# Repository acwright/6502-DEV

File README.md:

6502-DEV
========

An **AC6502** retro-style 8-bit computer based on the **65C02** microprocessor.

> 📖 **Guide:** [AC6502 Documentation](https://acwright.github.io/6502-DOCS/) — the user's and programmer's guide for the whole family.
> See [DEV's page in the family appendix](https://acwright.github.io/6502-DOCS/family/dev).

---

**Building one? Every part you need, with supplier numbers and known issues, is in [BOM.md](BOM.md).**

## Table of Contents

- [Overview](#overview)
- [Architecture](#architecture)
- [Systems](#systems)
- [Software](#software)
- [Hardware](#hardware)
  - [DEV Board](#dev-board)
  - [DEV Output Board](#dev-output-board)
  - [DEV LCD Board](#dev-lcd-board)
- [Which revision to make](#which-revision-to-make)
- [Works with the stock BIOS](#works-with-the-stock-bios)
- [Firmware](#firmware)
  - [DB Emulator](#db-emulator)
  - [DOB Display](#dob-display)
- [CAD](#cad)
- [Production](#production)
- [Schematics](#schematics)
- [Shared lines](#shared-lines)
- [Extra pins: `EXP0`–`EXP3` and `HRDB`](#extra-pins-exp0exp3-and-hrdb)
- [Jumpers](#jumpers)
- [Off-board headers](#off-board-headers)
- [Libraries](#libraries)
- [Bill of Materials](#bill-of-materials)
- [License](#license)

---

## Overview

The AC6502 ecosystem is a family of open-source, 65C02-based computers sharing a common architecture, memory map, and [BIOS](https://github.com/acwright/6502-BIOS). Each computer in the family is purpose-built for a different use case but runs the same software and firmware.

The **DEV** is an emulation-based development system. It replaces the physical 65C02 CPU with a [Teensy 4.1](https://www.pjrc.com/store/teensy41.html) running cycle-accurate 65C02 emulation via [vrEmu6502](https://github.com/visrealm/vrEmu6502).
## Architecture

All AC6502 computers share:

- **CPU**: 65C02 (or accurate emulation)
- **Memory**: 32KB RAM + 32KB ROM, with optional banked RAM expansion
- **Memory Map**: Standardized across the ecosystem — zero page, stack, I/O space ($8000–$9FFF), system ROM, and interrupt vectors at $FFFA–$FFFF
- **Bus**: 16-bit address bus, 8-bit bidirectional data bus, standard 65C02 control signals (RW, PHI2, RESET, IRQ, NMI, RDY, SYNC)
- **BIOS**: A common [BIOS](https://github.com/acwright/6502-BIOS) provides the kernel, monitor, and BASIC interpreter across all systems

## Systems

| Project | Description |
|---------|-------------|
| [6502-ACE](https://github.com/acwright/6502-ACE) | All-in-one Computer Experience — A single board computer |
| [6502-COB](https://github.com/acwright/6502-COB) | Computer On a Backplane — Modular desktop computer with expandable card slots |
| [6502-DEV](https://github.com/acwright/6502-DEV) | Development Environment Vehicle — Emulation-based dev system (YOU ARE HERE) |
| [6502-KIM](https://github.com/acwright/6502-KIM) | Keypad Input Monitor - KIM-1 inspired minimal computer |
| [6502-VCS](https://github.com/acwright/6502-VCS) | Video Computer System — Cartridge-based retro gaming console |

## Software

| Project | Description |
|---------|-------------|
| [6502-BIOS](https://github.com/acwright/6502-BIOS) | The shared BIOS (kernel, monitor, BASIC) for all AC6502 computers |
| [6502-EMULATOR](https://github.com/acwright/6502-EMULATOR) | Emulator for the whole family — desktop app, browser build, and a command line for scripted runs |
| [6502-PRG](https://github.com/acwright/6502-PRG) | Template project for writing assembly language programs |
| [6502-CRT](https://github.com/acwright/6502-CRT) | Template project for writing assembly language cartridges |
| [6502-ASM](https://github.com/acwright/6502-ASM) | Assembly language example programs and demos |
| [6502-BAS](https://github.com/acwright/6502-BAS) | BASIC program listings |
| [6502-WOZMON](https://github.com/acwright/6502-WOZMON) | Wozmon as a standalone ROM |
| [6502-NOP](https://github.com/acwright/6502-NOP) | An all-NOP ROM, for probing a board during bring-up |
| [6502-DOCS](https://github.com/acwright/6502-DOCS) | The documentation site — the guide, the printable reference cards, branding and label artwork |
| [cffs](https://github.com/acwright/cffs) | Builds CompactFlash disk images for the BIOS filesystem |
| [bastok](https://github.com/acwright/bastok) | Tokenizes BASIC listings into `.prg` images, and back |
| [bin2woz](https://github.com/acwright/bin2woz) | Converts a binary into a Wozmon serial upload |

## Hardware

This repository contains KiCad 7.0+ PCB designs for the boards of the DEV system: the two that make it up, and an LCD board for its bus.

### DEV Board
`Hardware/DEV Board/`

The main board hosting the Teensy 4.1. Provides 65C02 bus emulation, SD card storage, Ethernet, USB keyboard/joystick input, and hardware control buttons (Run/Stop, Step, Reset, Frequency). Includes a bus connector and card slot with level shifters for optional real hardware expansion.

### DEV Output Board
`Hardware/DEV Output Board/`

The AV output board hosting a Teensy 4.0 and a 2.4" ILI9341 TFT LCD. Emulates a TMS9918A Video Display Processor and a MOS 6581 SID audio synthesizer, driven in real time via high-speed serial from the DEV Board. The DEV Board sends the same AV packets over USB at the same time, so a browser can render the output in parallel with this board — the two paths are simultaneous, not alternatives.

### DEV LCD Board
`Hardware/DEV LCD Board/`

A 320×240 TFT LCD (an Adafruit 2.8" ILI9341 breakout) driven through a 65C22 VIA, on the AC6502 bus. Rev 1.0 was made as the COB LCD Board, and its silkscreen says `6502 LCD BOARD`; it moved here on 2026-11-14.

<!-- Which revision to make: generated by Tools/revision-audit/register.py from Tools/data/orders.json. Edit that file, not this section. -->
## Which revision to make

**Make the newest revision of a board, and check its label first.** The table below gives each board's newest revision. A newer revision fixes what was found on the older ones. Every revision, old and new, is in [REVISIONS.md](REVISIONS.md), with what changed in each.

Each revision carries one of three labels:

- **Tested:** This revision was built and tested.
- **Proven design:** Not built at this revision, but its circuit is proven. Either it is a tested revision's circuit, or each change copies a circuit built and tested on another board or on the bench, or is a textbook circuit that leaves everything the tested revision does as it was. Any other change is silkscreen text, part values, mounting holes, outline clean-up, parts moved a fraction of a millimetre onto their grid, capacitor pitch, socket outlines, a footprint swap with the same holes, a solder jumper's default, the solder mask or paste at a card edge, or tracks rerouted or pours refilled with DRC and the netlist check passing. A builder can treat it as tested.
- **Untested:** The circuit, the power path or the layout changed in a way that only a built board proves, or the board has never been built at all.

[BOM.md](BOM.md) has the parts for every revision, and its known issues.

| Board | Newest revision | Label | Why |
|---|---|---|---|
| DEV Board | 1.1 | **Proven design** | Rev 1.0's circuit, except that J6's CC resistors pull up to `5V_HOST` (56 kΩ), as a USB-C host's should, where Rev 1.0 pulls them down. Nothing Rev 1.0 was tested with changes. Two designators moved. |
| DEV LCD Board | 1.1 | **Proven design** | The DEV's name in the logo, JLCPCB's marker removed; silkscreen only. |
| DEV Output Board | 1.1 | **Proven design** | Silkscreen text only. |
<!-- End of which revision to make -->

<!-- Stock BIOS: generated by Tools/bios/gen.py from Tools/data/bios.json. Edit that file, not this section. -->
## Works with the stock BIOS

Whether each board works with the stock BIOS, and what it takes if not. The stock BIOS for the DEV is **BIOS 1.x**, from the `v1.x` branch of [6502-BIOS](https://github.com/acwright/6502-BIOS). The ACE runs BIOS 2.x, for a 6502-PICOVDP. The DEV can't run BIOS 2.x yet: its DB Emulator firmware is written for BIOS 1.x. The BIOS looks for each card in its own 1 KB window at boot, and uses only what it finds.

- **Compatible:** the BIOS finds the board and uses it, built from its parts list with the jumpers the [Jumpers](#jumpers) table gives. A card counts only on the window the BIOS expects; on another window it's the builder's experiment.
- **After a step:** it works once the builder does what the entry names, beyond the parts list and the jumpers.
- **Not used by the BIOS:** safe beside it, but your own software drives it.
- **Nothing to support:** the board has no registers for the BIOS to find, such as a backplane, a helper behind a card, or a cartridge's programmer.

| Board | Rev | Stock BIOS | Why | Source |
|---|---|---|---|---|
| DEV Board | 1.0, 1.1 | **Compatible** | Its Teensy 4.1 runs `BIOS.bin` from its SD card on an emulated 65C02, with every card the BIOS looks for emulated in its window, IO 1 to IO 8. | [DB Emulator](Firmware/DB%20Emulator/README.md) |
| DEV LCD Board | 1.0, 1.1 | **Not used by the BIOS** | The BIOS doesn't look for it: its 65C22 VIA goes in a window no other card uses, and your own software drives the LCD. | README [Jumpers](#jumpers) |
| DEV Output Board | 1.0, 1.1 | **Nothing to support** | No registers on the bus: it shows the DEV Board's emulated video and plays its emulated SID, sent over serial. | [DB Emulator](Firmware/DB%20Emulator/README.md) |

<!-- End of stock BIOS -->

## Firmware

This repository contains [PlatformIO](https://platformio.org/)-based firmware for both boards.

### DB Emulator
`Firmware/DB Emulator/`

Firmware for the Teensy 4.1 on the DEV Board. Provides:

- Cycle-accurate 65C02 emulation
- SD card ROM/cartridge/program loading and memory snapshots
- Ethernet with mDNS (`6502.local`) and an embedded web control interface
- USB keyboard and joystick support (Xbox 360/One)
- AV packet output to both destinations at once — over USB to the browser (Web Serial API) and over hardware UART at 6 Mbps to the DOB Display
- Serial terminal interface (115200 baud)
- Hardware button control (Run/Stop, Step, Reset, Frequency)
- Variable CPU clock speed

See [Firmware/DB Emulator/README.md](./Firmware/DB%20Emulator/README.md) for setup and usage instructions.

### DOB Display
`Firmware/DOB Display/`

Firmware for the Teensy 4.0 on the DEV Output Board. Provides:

- TMS9918A VDP emulation (all four display modes, 256×192 active area)
- MOS 6581 SID audio emulation (3 voices, ADSR envelopes, PWM audio output)
- AV packet stream input at 6 Mbps over hardware UART from the DB Emulator (which also streams the same packets over USB to the browser)

See [Firmware/DOB Display/README.md](./Firmware/DOB%20Display/README.md) for setup and usage instructions.

## CAD
`CAD/`

3D-printable enclosure parts and laser-cut top panels for the DEV system.

**Board images** are in `CAD/Images/<Board>/Rev X/`: `Front.png` and `Back.png` on white, and `Front Transparent.png` and `Back Transparent.png` with no background. Every image is a 3D render at the same size, with the black solder mask and white silkscreen the boards are made with. Bare-board photos may differ, because the renders show parts fitted.

**Top panels are versioned by board revision**, like `Hardware/`: `CAD/Tops/<Board>/Rev X/`. Each revision has its own complete folder, even when two revisions share the same files. `Bases/` holds the parts for a whole computer, not for one board, so it isn't versioned.

The **[plate mounting drawing](CAD/Bases/Plate%20Mounting%20Drawing.png)** ([SVG](CAD/Bases/Plate%20Mounting%20Drawing.svg)) shows where the DEV Board and the DEV Output Board mount on the base plate, with every hole's position and the hardware the build needs. The plate is a stack of three 3 mm acrylic layers.

## Production
`Production/`

[REVISIONS.md](REVISIONS.md) lists every board revision: whether it was made, its JLCPCB order, the commit it was made from, and what fits it.

JLCPCB-ready Gerber files and BOM/CPL for PCB fabrication and assembly.

## Schematics
`Schematics/`

PDF schematics for each board.

## Shared lines

Five lines of the 6502 bus are shared by every board on it: `RESB`, `IRQB`, `NMIB`, `RDY` and `BE`. A board may pull one of these lines low, and nothing drives one high. Each line is held high by one 10kΩ pull-up resistor to VCC, on the board with the CPU: the ACE Board, the KIM Board, the VCS Main Board, the COB CPU Card or CPU Card Pro, or the DEV Board. No other board has one. Two pull-ups on the same line would sit in parallel and lower its resistance, so a card that adds its own pull-up changes the machine for every other board. The VIAs and PIAs in the BOMs, the W65C22N and W65C21N, have open-drain interrupt outputs for this reason.

**Interrupt outputs.** Whatever drives `IRQB` or `NMIB` may only pull it low. Every board is drawn for the parts in its BOM and works as shipped, with no jumper to cut or bridge:

- **A part whose interrupt output is open-drain** (the W65C22N, W65C21N, R6551AP, DS1511Y, DS1501 and TMS9918A) drives the line directly, or through a diode with a solder jumper across it that ships bridged. The diode is fitted either way. To use a part that drives its interrupt high as well as low instead, such as a W65C22S or a replacement of your own, cut the jumper: the diode then lets the part only pull the line low. A board with no diode in the line can't take such a part.
- **A part that drives its interrupt high as well as low** (the pico9918, the VERA module, and a microcontroller such as the ATmega1284 or a Raspberry Pi Pico) reaches the line through a diode, a BAT85 or a 1N914, with its cathode toward the part. Where a solder jumper sits across that diode, it ships open. The diode is then the only path to the line, so fit it, and never bridge the jumper, because the part would then hold the line high against every other interrupt source.
- **A microcontroller wired to the line directly,** as on the ACE Board, the Mega Helper and the Flash Helper, drives it open-drain in its firmware: it sets the pin low or leaves it as an input, and never drives it high.

The *Jumpers* section below gives each board's interrupt jumper.

The same holds where a board has its own reset circuit. A reset switch, its timer and the transistor that pulls `RESB` low can be on any board, such as the COB Backplane Pro or the Clock Card, but the `RESB` pull-up is only ever on the board with the CPU. Each of those boards draws its pull-ups together, in one group on its schematic.

The DEV Board is the exception on `RESB`. It stands in for a Main Board, so it owns reset: its Reset button goes to the Teensy, and the Teensy drives `RESB` onto the bus through U3, a level shifter that only sends signals out, as it drives `PHI2`. U3 holds `RESB` high or low, so the DEV Board has no `RESB` pull-up, and nothing else on its bus may pull `RESB` low. Connect a DEV only to a passive backplane, never to the COB Backplane Pro, whose reset circuit would pull against U3, and don't fit a card that pulls `RESB` low, such as the COB RTC Card.

`SOB` is a CPU pin that isn't on the bus. It is tied to VCC, directly or through a 10kΩ resistor.

A few chips have a pull-up of their own inside the chip, such as an ATmega's reset pin. Where such a pin is wired to `RESB`, its pull-up of 30–60kΩ sits in parallel with the 10kΩ one. That's harmless, because whatever pulls `RESB` low can sink the extra current many times over.

A revision that doesn't follow this yet says so in its known issues in [BOM.md](BOM.md), with what to fit or remove.

## Extra pins: `EXP0`–`EXP3` and `HRDB`

`EXP` stands for "extra pin". Four pins of the 6502 bus are left for a builder's own use: pin 4 is `EXP1`, pin 6 is `EXP0`, pin 19 is `EXP3` and pin 21 is `EXP2`.

Pins 4 and 6 have a second job. A cartridge ties both of them to GND. That pulls `HRDB` ("High ROM disable bar", active low) low on the board with the ROM, which takes `$C000–$FFFF` away from the ROM so that the cartridge answers there instead. So in a build that uses cartridges, pins 4 and 6 are reserved for `HRDB`, and nothing else may drive them. They are free as `EXP1` and `EXP0` only in a build that never uses cartridges. `EXP2` and `EXP3` are always free.

How the boards treat pins 4 and 6:

- **The ACE Board and the KIM Board** join them to their ROM's `HRDB` input, and their silk says `HRDB`. The VCS Main Board joins them the same way from Rev 1.1.
- **The COB Memory Card** joins them to its `HRDB` only through jumpers: fit two shunts on J2, or bridge JP1 and JP2, in a COB that takes cartridges. It is the only board with these jumpers, because the COB is the experimenter's build. The VCS Main Board Rev 1.0 had them too (J5, or JP3 and JP4); fit them, because the VCS always takes cartridges.
- **A cartridge** (the ROM Cart, the Flash Cart, the KIM Keypad Card) ties them to GND.
- **A board that only carries the bus through**, such as a backplane or a helper, calls them `EXP1` and `EXP0`, as its silk does, and a note on its schematic says what they carry.

<!-- Jumpers: generated by Tools/jumpers/gen.py from Tools/data/jumpers.json. Edit that file, not this section. -->
## Jumpers

Some boards have solder jumpers, and pin headers that take a shunt. The tables below give every one: what it's for, how the board is shipped, and what to do with it. The **Needed** column marks the ones that matter:

- **To run**: the board doesn't work until this is set. Set it before the first power-up.
- **For serial**, **For interrupts**, **For cartridges**: the board runs without it, but that feature doesn't.
- Blank: leave it as shipped unless you want what it offers.

Where a header needs a shunt, the board's BOM lists it.

**DEV LCD Board**

| Rev | Jumper | What it's for | As shipped | What to do | Needed |
|---|---|---|---|---|---|
| 1.0, 1.1 | J2 | I/O window: one shunt picks the 1 KB window the board answers in. | No shunt. | Fit the shunt beside a window no other card uses. The BIOS doesn't look for this board. | To run |
| 1.0, 1.1 | JP1 | Across D2, the diode in the W65C22N's interrupt line. | Bridged. | Leave it. The W65C22N's interrupt output is open-drain: it only pulls the line low, so the board works as shipped and D2 isn't needed. To fit a part that drives its interrupt high as well as low, such as a W65C22S, cut JP1 so the interrupt goes through D2. |  |

<!-- End of jumpers -->

<!-- Off-board headers: generated by Tools/offboard/gen.py from Tools/offboard/offboard.json, Tools/data/offboard.json and the PCB files. Edit those, not this section. -->
## Off-board headers

Some boards have small headers, such as `RESET SW`, `CLOCK ENBL SW`, `POWER LED` and `VCC`, that a standard build leaves empty. They are for a machine built into a full enclosure, which AC6502 doesn't offer today. In such a build, the parts a person handles are mounted on the case and wired to the board through these headers: the power jack, the switches, the LEDs and the keyboard. The matching parts on the board are then left off. For example, an ACE Board can sit inside a case with its power jack, power switch and key switches left off, and a Keyboard Helper as its keyboard.

To build a board for a case:

1. Fit the header, and wire the part on the case to it. The table says what goes on each pin.
2. Leave off the parts on the board that the table names. A button on the case can work beside the board's own button, but some parts, such as an LED that shares the board's resistor, can't share.
3. Set any jumper the table mentions. The [Jumpers](#jumpers) section has the rest.

The connector follows the kind of build. A single-board machine, the ACE Board or the KIM Board, uses plain 2.54 mm pin headers, which are simpler and cheaper. A board in a multi-board machine, every COB board and the separate boards of the VCS, the DEV and the KIM, uses JST XH, the family's standard for these headers.

The table lists every off-board header on each board's newest revision, read from the board's PCB file.

| Board | Rev | Header | Label | Connector | What it's for | Leave off |
|---|---|---|---|---|---|---|
| DEV Board | 1.1 | J3 | `PANEL` | Pin header, 2×4, 2.54 mm | Four buttons on the case, each between its pin and ground: Run/Stop on pin 1, Step on pin 3, Clock on pin 5 and Reset on pin 7. Pins 2, 4, 6 and 8 are ground. Each button is wired across one of SW1–SW4, the board's own buttons. | SW1–SW4, if the case covers them. Both sets of buttons work if they stay. |

<!-- End of off-board headers -->

## Libraries
`Libraries/`

Shared KiCad symbol and footprint libraries used across all AC6502 hardware projects, with their 3D models in `Models/`. A part is named for what it is and its shape, such as `RJ45 Jack LED` or `CR2032 Holder`, never for a manufacturer's part number, so a replacement part with the same footprint fits without renaming anything. The part numbers to buy are in [BOM.md](BOM.md). Every AC6502 repository carries the same copy of each part.

## Bill of Materials

Every part for every board, by revision, is in **[BOM.md](BOM.md)**, with supplier numbers, known issues, build notes and files to upload to Digi-Key and Mouser. What changed in each revision, and what is known about each one, is in **[REVISIONS.md](REVISIONS.md)**.

## License

Hardware designs are released under the [CERN Open Hardware Licence Version 2 – Permissive](https://ohwr.org/cern_ohl_p_v2.txt).  
Firmware is released under the MIT License — [DB Emulator](./Firmware/DB%20Emulator/LICENSE), [DOB Display](./Firmware/DOB%20Display/LICENSE).

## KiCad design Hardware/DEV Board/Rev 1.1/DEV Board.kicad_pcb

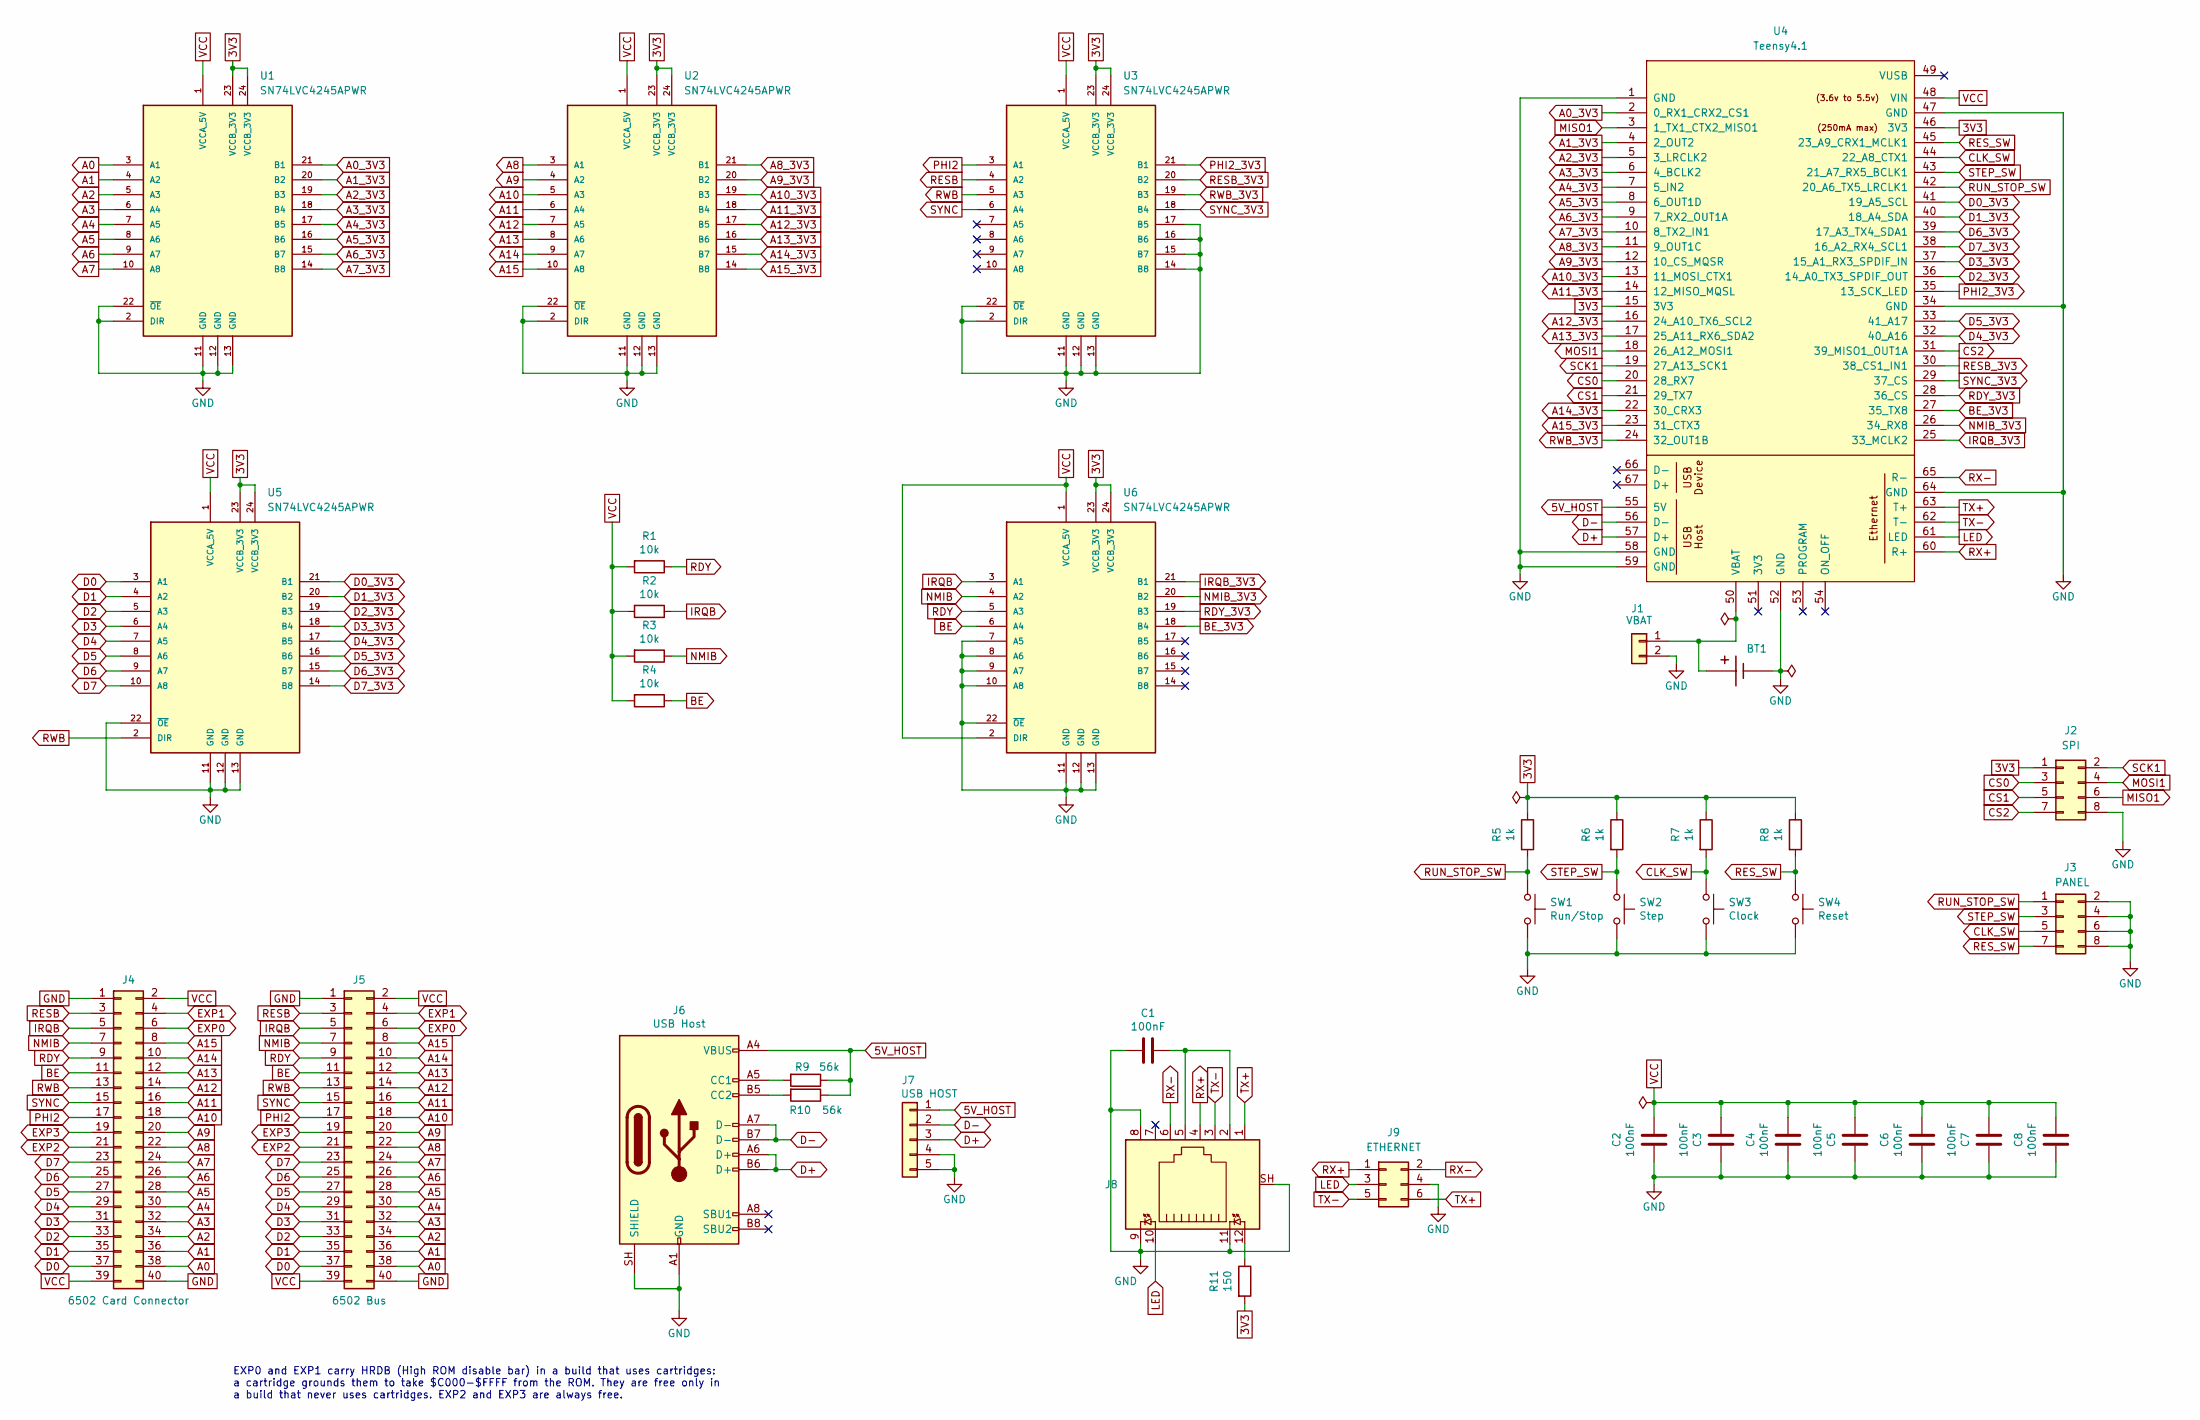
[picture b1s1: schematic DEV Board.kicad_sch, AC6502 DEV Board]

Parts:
BT1: CR2032; CR2032 Holder; Digikey 343-BAT-HLD-001-THM-TRCT-ND
C1, C2, C3, C4, C5, C6, C7, C8: 100nF; C_0805_2012Metric; LCSC C49678
J1: VBAT; PinHeader_1x02_P2.54mm_Vertical; Digikey S1011EC-40-ND
J2: SPI; PinHeader_2x04_P2.54mm_Vertical; Digikey S2011EC-40-ND
J3: PANEL; PinHeader_2x04_P2.54mm_Vertical; Digikey S2011EC-40-ND
J4: 6502 Card Connector; 6502 Card Slot; Digikey A31723-ND
J5: 6502 Bus; 6502 Bus Connector; Digikey 732-5401-ND
J6: USB Host; USB_C_Receptacle_HRO_TYPE-C-31-M-12; LCSC C2988369
J7: USB HOST; PinHeader_1x05_P2.54mm_Vertical; Digikey S1011EC-40-ND
J8: RJ45_LED; RJ45 Jack LED; Digikey 931-TMJDD111B083FC2A1D-ND
J9: ETHERNET; PinHeader_2x03_P2.00mm_Vertical; Digikey 2057-2PH2-06-UA-ND
R1, R2, R3, R4: 10k; R_0805_2012Metric; LCSC C17414
R5, R6, R7, R8: 1k; R_0805_2012Metric; LCSC C17513
R9, R10: 56k; R_0805_2012Metric; LCSC C169923
R11: 150; R_0805_2012Metric; LCSC C17471
SW1: Run/Stop; Tact Switch SMD 5.1mm; LCSC C318884
SW2: Step; Tact Switch SMD 5.1mm; LCSC C318884
SW3: Clock; Tact Switch SMD 5.1mm; LCSC C318884
SW4: Reset; Tact Switch SMD 5.1mm; LCSC C318884
U1, U2, U3, U5, U6: SN74LVC4245APWR; TSSOP-24_4.4x7.8mm_P0.65mm; LCSC C7859
U4: Teensy4.1; Teensy41

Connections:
3V3: J2.1, R5.1, R6.1, R7.1, R8.1, R11.2, U1.23 (VCCB_3V3), U1.24 (VCCB_3V3), U2.23 (VCCB_3V3), U2.24 (VCCB_3V3), U3.23 (VCCB_3V3), U3.24 (VCCB_3V3), U4.15 (3V3), U4.46 (3V3), U5.23 (VCCB_3V3), U5.24 (VCCB_3V3), U6.23 (VCCB_3V3), U6.24 (VCCB_3V3)
5V_HOST: J6.A4 (VBUS), J6.A9 (VBUS), J6.B4 (VBUS), J6.B9 (VBUS), J7.1, R9.1, R10.1, U4.55 (5V)
A0: J4.38, J5.38, U1.3 (A1)
A0_3V3: U1.21 (B1), U4.2 (0_RX1_CRX2_CS1)
A1: J4.36, J5.36, U1.4 (A2)
A1_3V3: U1.20 (B2), U4.4 (2_OUT2)
A2: J4.34, J5.34, U1.5 (A3)
A2_3V3: U1.19 (B3), U4.5 (3_LRCLK2)
A3: J4.32, J5.32, U1.6 (A4)
A3_3V3: U1.18 (B4), U4.6 (4_BCLK2)
A4: J4.30, J5.30, U1.7 (A5)
A4_3V3: U1.17 (B5), U4.7 (5_IN2)
A5: J4.28, J5.28, U1.8 (A6)
A5_3V3: U1.16 (B6), U4.8 (6_OUT1D)
A6: J4.26, J5.26, U1.9 (A7)
A6_3V3: U1.15 (B7), U4.9 (7_RX2_OUT1A)
A7: J4.24, J5.24, U1.10 (A8)
A7_3V3: U1.14 (B8), U4.10 (8_TX2_IN1)
A8: J4.22, J5.22, U2.3 (A1)
A8_3V3: U2.21 (B1), U4.11 (9_OUT1C)
A9: J4.20, J5.20, U2.4 (A2)
A9_3V3: U2.20 (B2), U4.12 (10_CS_MQSR)
A10: J4.18, J5.18, U2.5 (A3)
A10_3V3: U2.19 (B3), U4.13 (11_MOSI_CTX1)
A11: J4.16, J5.16, U2.6 (A4)
A11_3V3: U2.18 (B4), U4.14 (12_MISO_MQSL)
A12: J4.14, J5.14, U2.7 (A5)
A12_3V3: U2.17 (B5), U4.16 (24_A10_TX6_SCL2)
A13: J4.12, J5.12, U2.8 (A6)
A13_3V3: U2.16 (B6), U4.17 (25_A11_RX6_SDA2)
A14: J4.10, J5.10, U2.9 (A7)
A14_3V3: U2.15 (B7), U4.22 (30_CRX3)
A15: J4.8, J5.8, U2.10 (A8)
A15_3V3: U2.14 (B8), U4.23 (31_CTX3)
BE: J4.11, J5.11, R4.1, U6.6 (A4)
BE_3V3: U4.27 (35_TX8), U6.18 (B4)
CLK_SW: J3.5, R7.2, SW3.1, U4.44 (22_A8_CTX1)
CS0: J2.3, U4.20 (28_RX7)
CS1: J2.5, U4.21 (29_TX7)
CS2: J2.7, U4.31 (39_MISO1_OUT1A)
D0: J4.37, J5.37, U5.3 (A1)
D0_3V3: U4.41 (19_A5_SCL), U5.21 (B1)
D1: J4.35, J5.35, U5.4 (A2)
D1_3V3: U4.40 (18_A4_SDA), U5.20 (B2)
D2: J4.33, J5.33, U5.5 (A3)
D2_3V3: U4.36 (14_A0_TX3_SPDIF_OUT), U5.19 (B3)
D3: J4.31, J5.31, U5.6 (A4)
D3_3V3: U4.37 (15_A1_RX3_SPDIF_IN), U5.18 (B4)
D4: J4.29, J5.29, U5.7 (A5)
D4_3V3: U4.32 (40_A16), U5.17 (B5)
D5: J4.27, J5.27, U5.8 (A6)
D5_3V3: U4.33 (41_A17), U5.16 (B6)
D6: J4.25, J5.25, U5.9 (A7)
D6_3V3: U4.39 (17_A3_TX4_SDA1), U5.15 (B7)
D7: J4.23, J5.23, U5.10 (A8)
D7_3V3: U4.38 (16_A2_RX4_SCL1), U5.14 (B8)
D+: J6.A6 (D+), J6.B6 (D+), J7.3, U4.57 (D+)
D-: J6.A7 (D-), J6.B7 (D-), J7.2, U4.56 (D-)
EXP0: J4.6, J5.6
EXP1: J4.4, J5.4
EXP2: J4.21, J5.21
EXP3: J4.19, J5.19
GND: BT1.-, C1.2, C2.2, C3.1, C4.2, C5.1, C6.2, C7.1, C8.2, J1.2, J2.8, J3.2, J3.4, J3.6, J3.8, J4.1, J4.40, J5.1, J5.40, J6.A1 (GND), J6.A12 (GND), J6.B1 (GND), J6.B12 (GND), J6.SH (SHIELD), J7.4, J7.5, J8.8, J8.9, J8.11, J8.SH, J9.4, SW1.2, SW2.2, SW3.2, SW4.2, U1.2 (DIR), U1.11 (GND), U1.12 (GND), U1.13 (GND), U1.22 (~OE), U2.2 (DIR), U2.11 (GND), U2.12 (GND), U2.13 (GND), U2.22 (~OE), U3.2 (DIR), U3.11 (GND), U3.12 (GND), U3.13 (GND), U3.14 (B8), U3.15 (B7), U3.16 (B6), U3.17 (B5), U3.22 (~OE), U4.1 (GND), U4.34 (GND), U4.47 (GND), U4.52 (GND), U4.58 (GND), U4.59 (GND), U4.64 (GND), U5.11 (GND), U5.12 (GND), U5.13 (GND), U5.22 (~OE), U6.7 (A5), U6.8 (A6), U6.9 (A7), U6.10 (A8), U6.11 (GND), U6.12 (GND), U6.13 (GND), U6.22 (~OE)
IRQB: J4.5, J5.5, R2.1, U6.3 (A1)
IRQB_3V3: U4.25 (33_MCLK2), U6.21 (B1)
LED: J8.10, J9.3, U4.61 (LED)
MISO1: J2.6, U4.3 (1_TX1_CTX2_MISO1)
MOSI1: J2.4, U4.18 (26_A12_MOSI1)
NMIB: J4.7, J5.7, R3.1, U6.4 (A2)
NMIB_3V3: U4.26 (34_RX8), U6.20 (B2)
unnamed: C1.1, J8.2, J8.5
unnamed: BT1.+, J1.1, U4.50 (VBAT)
unnamed: J6.A5 (CC1), R9.2
unnamed: J6.B5 (CC2), R10.2
unnamed: J8.12, R11.1
PHI2: J4.17, J5.17, U3.3 (A1)
PHI2_3V3: U3.21 (B1), U4.35 (13_SCK_LED)
RDY: J4.9, J5.9, R1.1, U6.5 (A3)
RDY_3V3: U4.28 (36_CS), U6.19 (B3)
RESB: J4.3, J5.3, U3.4 (A2)
RESB_3V3: U3.20 (B2), U4.30 (38_CS1_IN1)
RES_SW: J3.7, R8.2, SW4.1, U4.45 (23_A9_CRX1_MCLK1)
RUN_STOP_SW: J3.1, R5.2, SW1.1, U4.42 (20_A6_TX5_LRCLK1)
RWB: J4.13, J5.13, U3.5 (A3), U5.2 (DIR)
RWB_3V3: U3.19 (B3), U4.24 (32_OUT1B)
RX+: J8.4, J9.1, U4.60 (R+)
RX-: J8.6, J9.2, U4.65 (R-)
SCK1: J2.2, U4.19 (27_A13_SCK1)
STEP_SW: J3.3, R6.2, SW2.1, U4.43 (21_A7_RX5_BCLK1)
SYNC: J4.15, J5.15, U3.6 (A4)
SYNC_3V3: U3.18 (B4), U4.29 (37_CS)
TX+: J8.1, J9.6, U4.63 (T+)
TX-: J8.3, J9.5, U4.62 (T-)
VCC: C2.1, C3.2, C4.1, C5.2, C6.1, C7.2, C8.1, J4.2, J4.39, J5.2, J5.39, R1.2, R2.2, R3.2, R4.2, U1.1 (VCCA_5V), U2.1 (VCCA_5V), U3.1 (VCCA_5V), U4.48 (VIN), U5.1 (VCCA_5V), U6.1 (VCCA_5V), U6.2 (DIR)

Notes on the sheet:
EXP0 and EXP1 carry HRDB (High ROM disable bar) in a build that uses cartridges: a cartridge grounds them to take $C000-$FFFF from the ROM. They are free only in a build that never uses cartridges. EXP2 and EXP3 are always free.

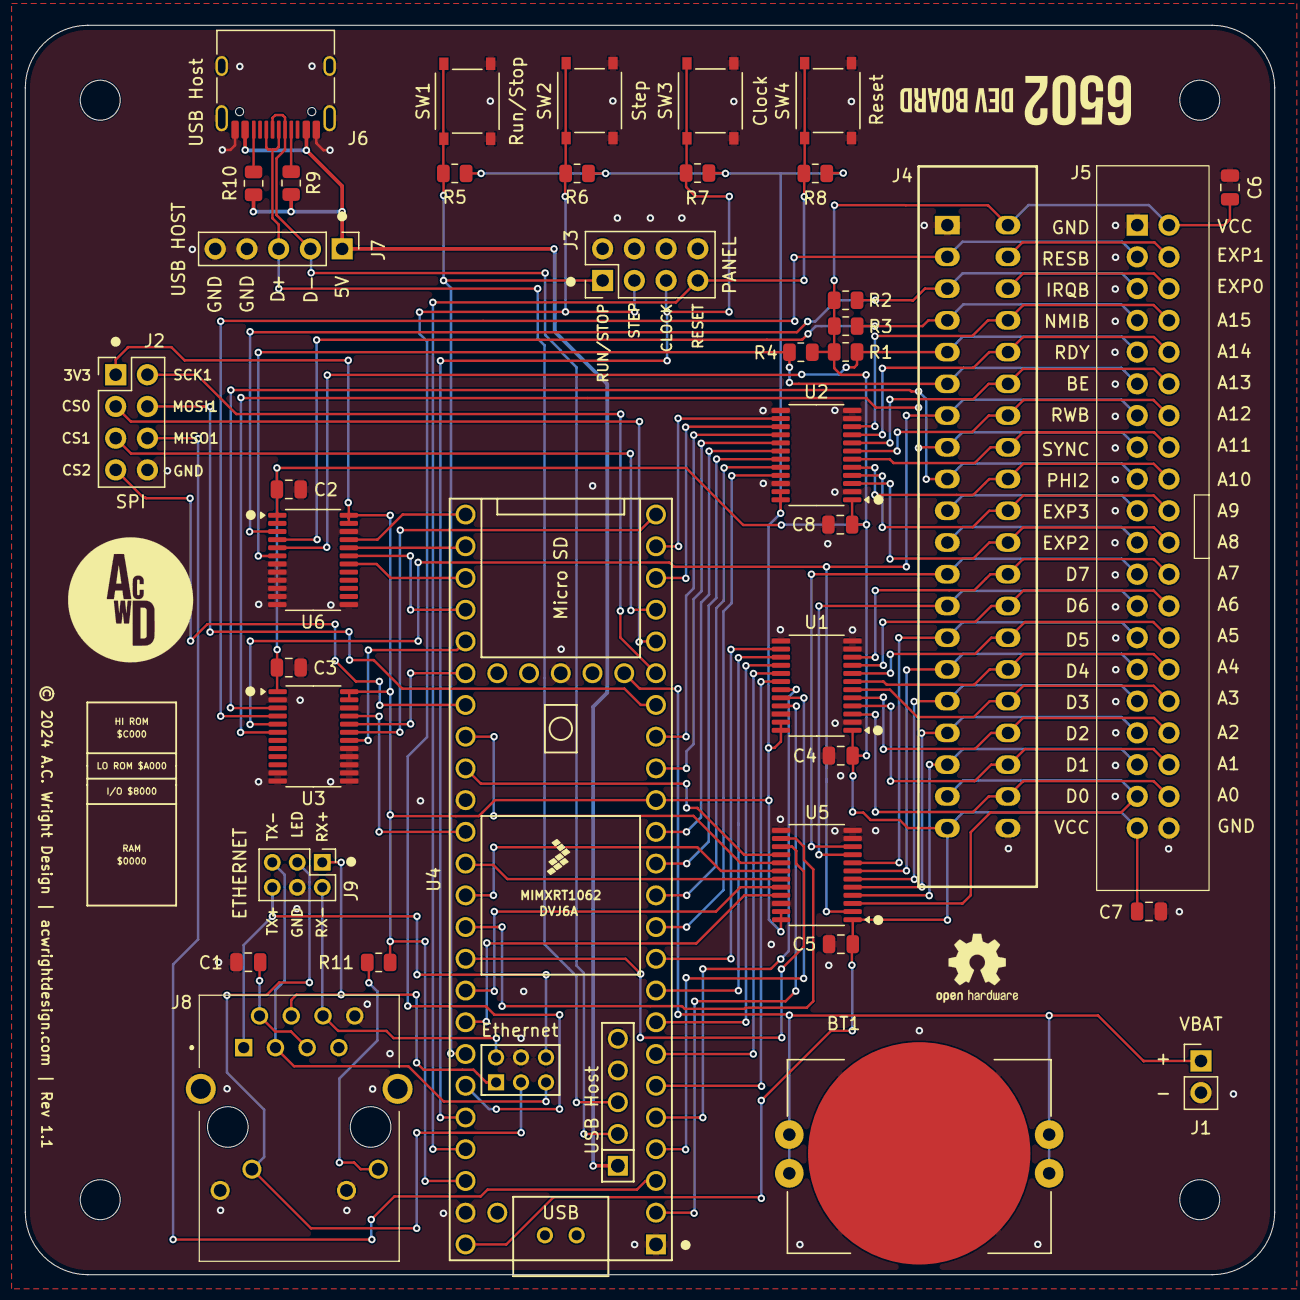
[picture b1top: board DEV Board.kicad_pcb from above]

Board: 2 copper layers, 100.0 x 100.0 mm, 43 parts (0 on the bottom side), 94 nets.

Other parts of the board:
H1, H2, H3, H4: MountingHole; MountingHole_3.2mm_M3

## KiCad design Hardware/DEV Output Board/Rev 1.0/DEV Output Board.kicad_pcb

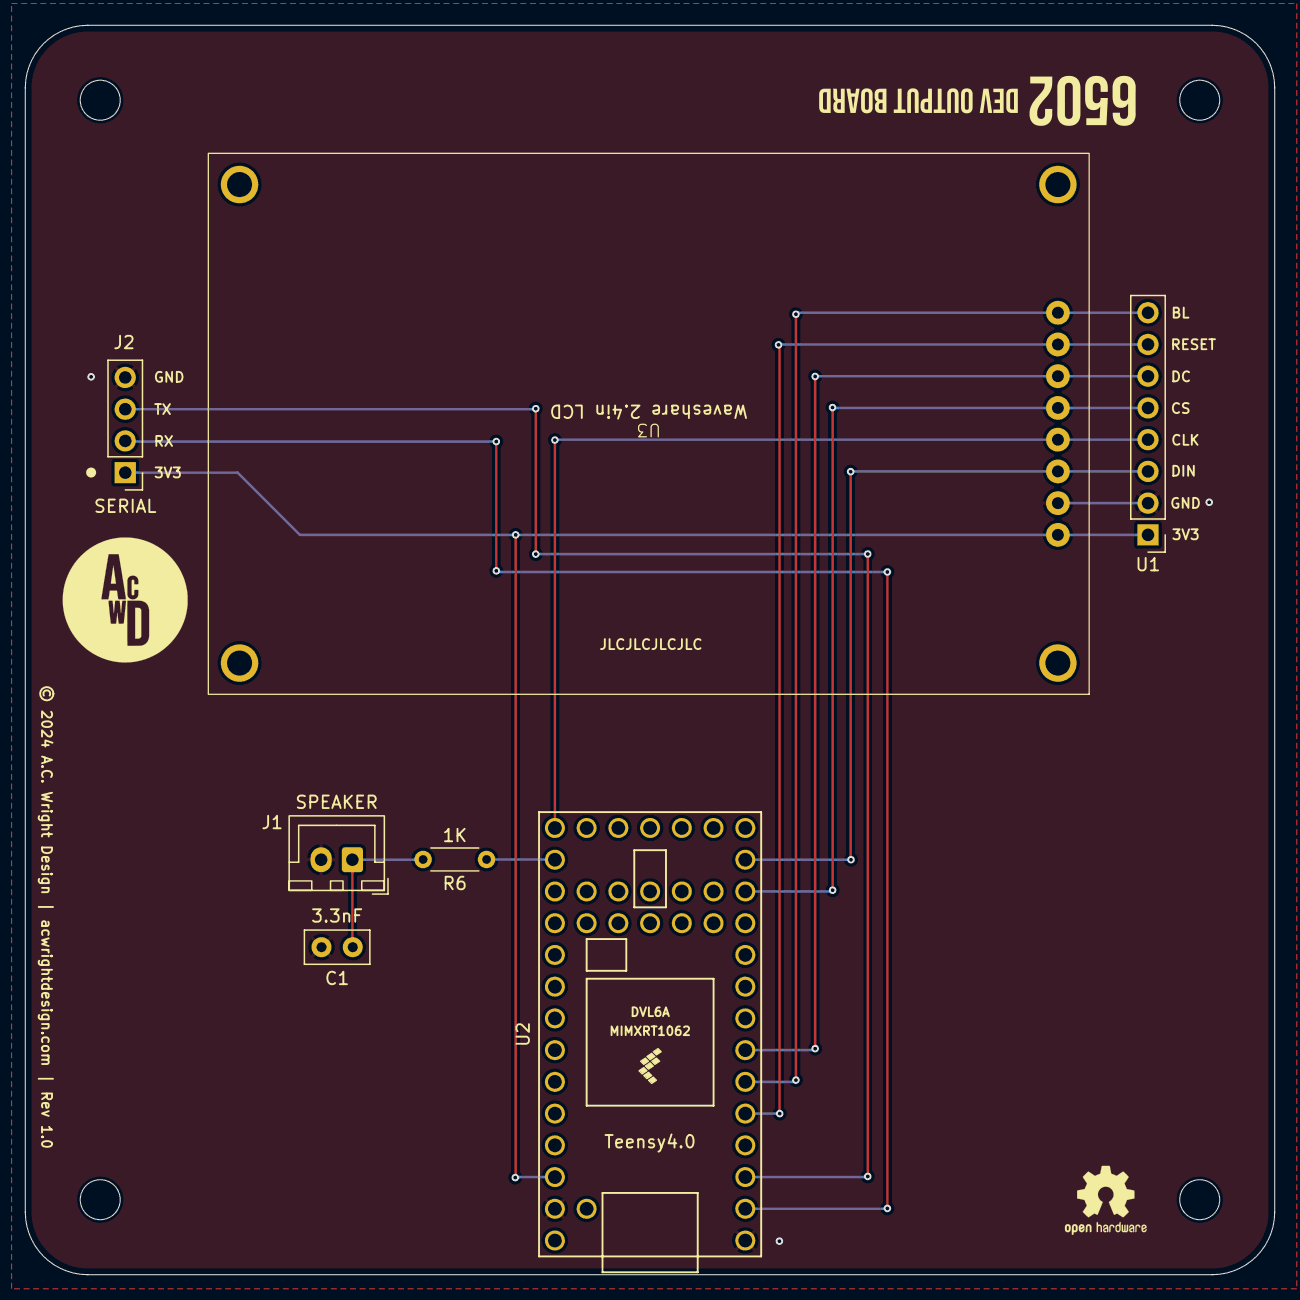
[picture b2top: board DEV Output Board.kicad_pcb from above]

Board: 2 copper layers, 100.0 x 100.0 mm, 11 parts (0 on the bottom side), 12 nets.

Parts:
C1: 3.3nF; C_Disc_D5.0mm_W2.5mm_P2.50mm
H1, H2, H3, H4: MountingHole; MountingHole_3.2mm_M3
J1: SPEAKER; JST_XH_B2B-XH-A_1x02_P2.50mm_Vertical
J2: SERIAL; PinHeader_1x04_P2.54mm_Vertical
R6: 1K; R_Axial_DIN0204_L3.6mm_D1.6mm_P5.08mm_Horizontal
U1: Waveshare 2.4in LCD Header; PinHeader_1x08_P2.54mm_Vertical
U2: Teensy4.0; Teensy40
U3: Waveshare 2.4in LCD

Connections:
3V3: J2.1, U1.1 (VCC), U2.31 (3V3), U3.1 (VCC)
GND: C1.2, J1.2, J2.4, U1.2 (GND), U2.1 (GND), U2.32 (GND), U3.2 (GND)
LCD_BL: U1.8 (BL), U2.6 (4_BCLK2), U3.8 (BL)
LCD_CLK: U1.4 (CLK), U2.20 (13_SCK_CRX1_LED), U3.4 (CLK)
LCD_CS: U1.5 (CS), U2.12 (10_CS_MQSR), U3.5 (CS)
LCD_DATA: U1.3 (DIN), U2.13 (11_MOSI_CTX1), U3.3 (DIN)
LCD_DC: U1.6 (DC), U2.7 (5_IN2), U3.6 (DC)
LCD_RESET: U1.7 (RST), U2.5 (3_LRCLK2), U3.7 (RST)
unnamed: C1.1, J1.1, R6.2
RX: J2.2, U2.2 (0_RX1_CRX2_CS1)
SPEAKER: R6.1, U2.21 (14_A0_TX3_SPDIF_OUT)
TX: J2.3, U2.3 (1_TX1_CTX2_MISO1)

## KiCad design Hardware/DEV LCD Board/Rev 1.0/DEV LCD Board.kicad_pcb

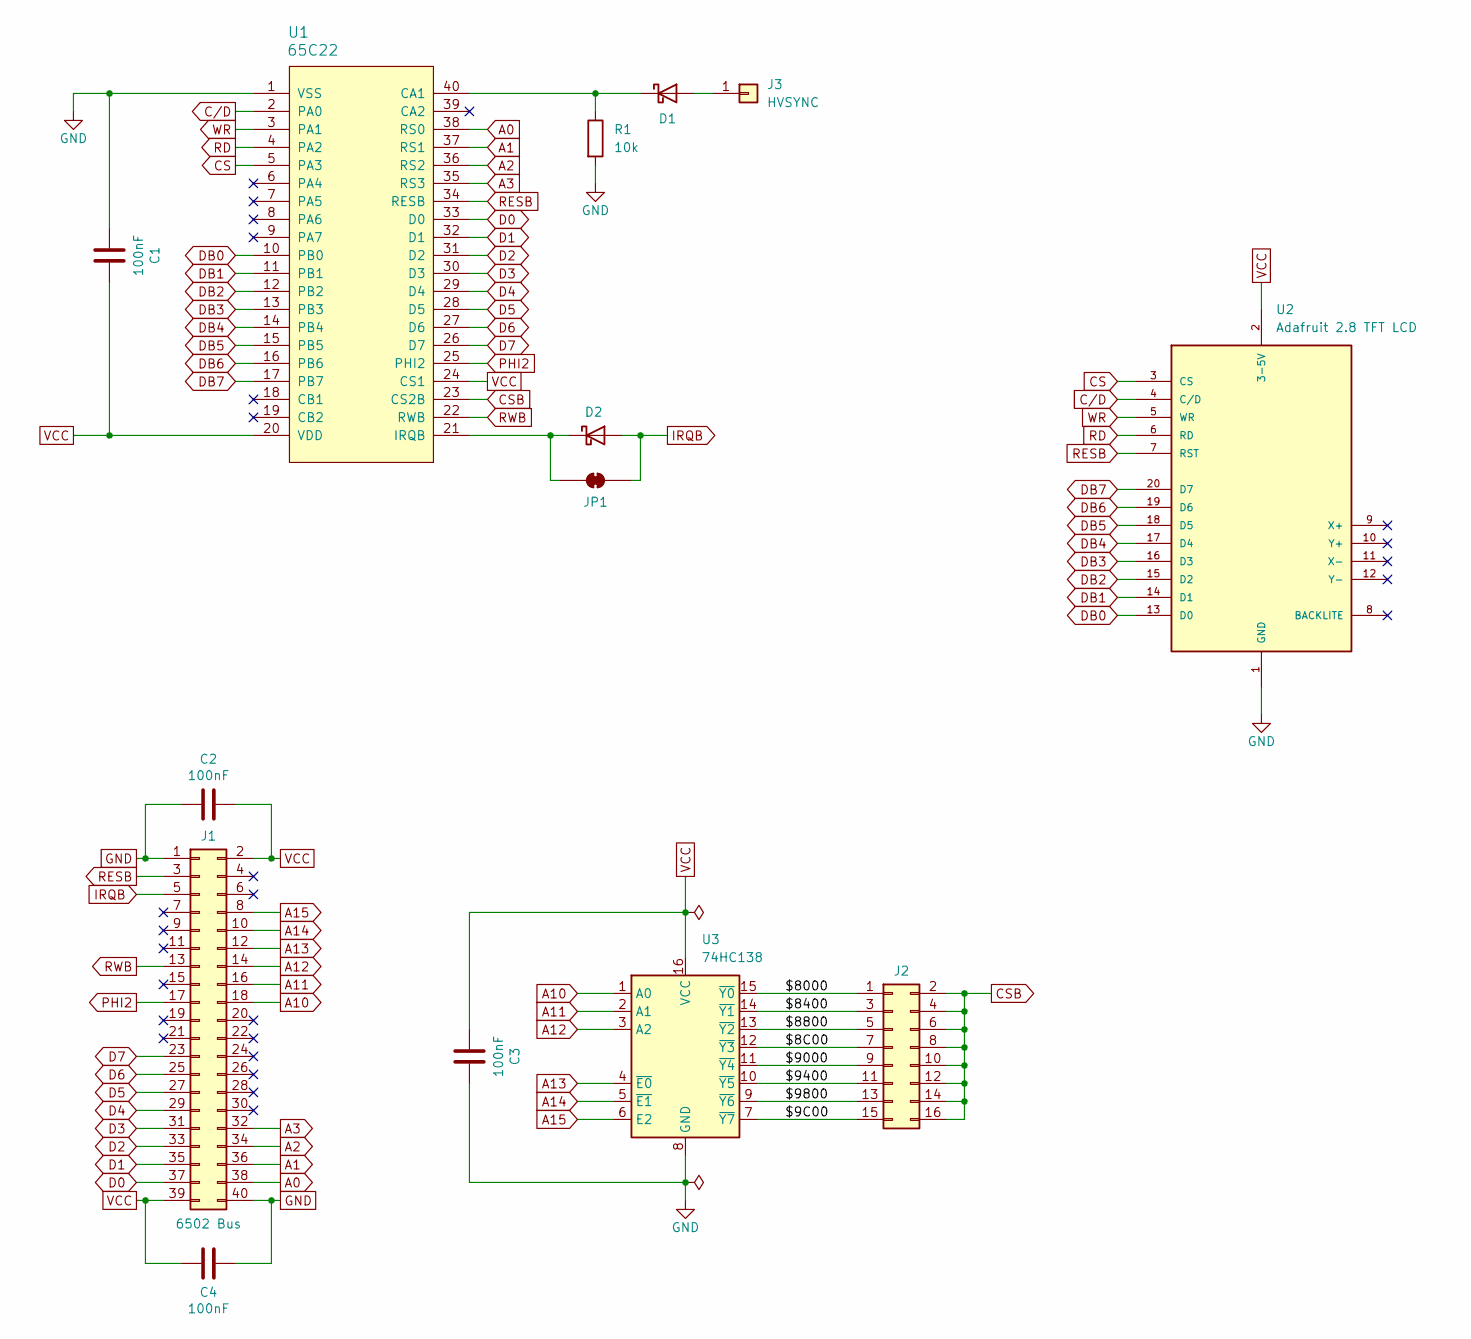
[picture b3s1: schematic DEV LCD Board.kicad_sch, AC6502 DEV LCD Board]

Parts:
C1, C2, C3, C4: 100nF; C_Disc_D5.0mm_W2.5mm_P2.50mm; Digikey 478-3187-ND
D1, D2: BAT85; D_DO-35_SOD27_P7.62mm_Horizontal; Digikey BAT85SCT-ND
J1: 6502 Bus; 6502 Bus Connector; Digikey 732-5401-ND
J2: Conn_02x08_Odd_Even; PinHeader_2x08_P2.54mm_Vertical; Digikey S2011EC-40-ND
J3: HVSYNC; PinHeader_1x01_P2.54mm_Vertical; Digikey S1011EC-40-ND
JP1: SolderJumper_2_Bridged; SolderJumper-2_P1.3mm_Bridged_RoundedPad1.0x1.5mm
R1: 10k; R_Axial_DIN0204_L3.6mm_D1.6mm_P5.08mm_Horizontal; Digikey 13-MFR-12FTF52-10KCT-ND
U1: 65C22; DIP-40_W15.24mm_Socket_LongPads; Mouser 955-W65C22N6TPG-14
U2: Adafruit 2.8 TFT LCD
U3: 74HC138; DIP-16_W7.62mm_Socket_LongPads; Digikey 296-1575-5-ND

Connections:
/$8C00: J2.7, U3.12 (~Y3)
/$9C00: J2.15, U3.7 (~Y7)
/$8000: J2.1, U3.15 (~Y0)
/$8400: J2.3, U3.14 (~Y1)
/$8800: J2.5, U3.13 (~Y2)
/$9000: J2.9, U3.11 (~Y4)
/$9400: J2.11, U3.10 (~Y5)
/$9800: J2.13, U3.9 (~Y6)
A0: J1.38, U1.38 (RS0)
A1: J1.36, U1.37 (RS1)
A2: J1.34, U1.36 (RS2)
A3: J1.32, U1.35 (RS3)
A10: J1.18, U3.1 (A0)
A11: J1.16, U3.2 (A1)
A12: J1.14, U3.3 (A2)
A13: J1.12, U3.4 (~E0)
A14: J1.10, U3.5 (~E1)
A15: J1.8, U3.6 (E2)
CS: U1.5 (PA3), U2.3 (CS)
CSB: J2.2, J2.4, J2.6, J2.8, J2.10, J2.12, J2.14, J2.16, U1.23 (CS2B)
C/D: U1.2 (PA0), U2.4 (C/D)
D0: J1.37, U1.33 (D0)
D1: J1.35, U1.32 (D1)
D2: J1.33, U1.31 (D2)
D3: J1.31, U1.30 (D3)
D4: J1.29, U1.29 (D4)
D5: J1.27, U1.28 (D5)
D6: J1.25, U1.27 (D6)
D7: J1.23, U1.26 (D7)
DB0: U1.10 (PB0), U2.13 (D0)
DB1: U1.11 (PB1), U2.14 (D1)
DB2: U1.12 (PB2), U2.15 (D2)
DB3: U1.13 (PB3), U2.16 (D3)
DB4: U1.14 (PB4), U2.17 (D4)
DB5: U1.15 (PB5), U2.18 (D5)
DB6: U1.16 (PB6), U2.19 (D6)
DB7: U1.17 (PB7), U2.20 (D7)
GND: C1.1, C2.2, C3.2, C4.1, J1.1, J1.40, R1.2, U1.1 (VSS), U2.1 (GND), U3.8 (GND)
IRQB: D2.2 (A), J1.5, JP1.2 (B)
unnamed: D1.2 (A), J3.1
unnamed: D1.1 (K), R1.1, U1.40 (CA1)
unnamed: D2.1 (K), JP1.1 (A), U1.21 (IRQB)
PHI2: J1.17, U1.25 (PHI2)
RD: U1.4 (PA2), U2.6 (RD)
RESB: J1.3, U1.34 (RESB), U2.7 (RST)
RWB: J1.13, U1.22 (RWB)
VCC: C1.2, C2.1, C3.1, C4.2, J1.2, J1.39, U1.20 (VDD), U1.24 (CS1), U2.2 (3-5V), U3.16 (VCC)
WR: U1.3 (PA1), U2.5 (WR)

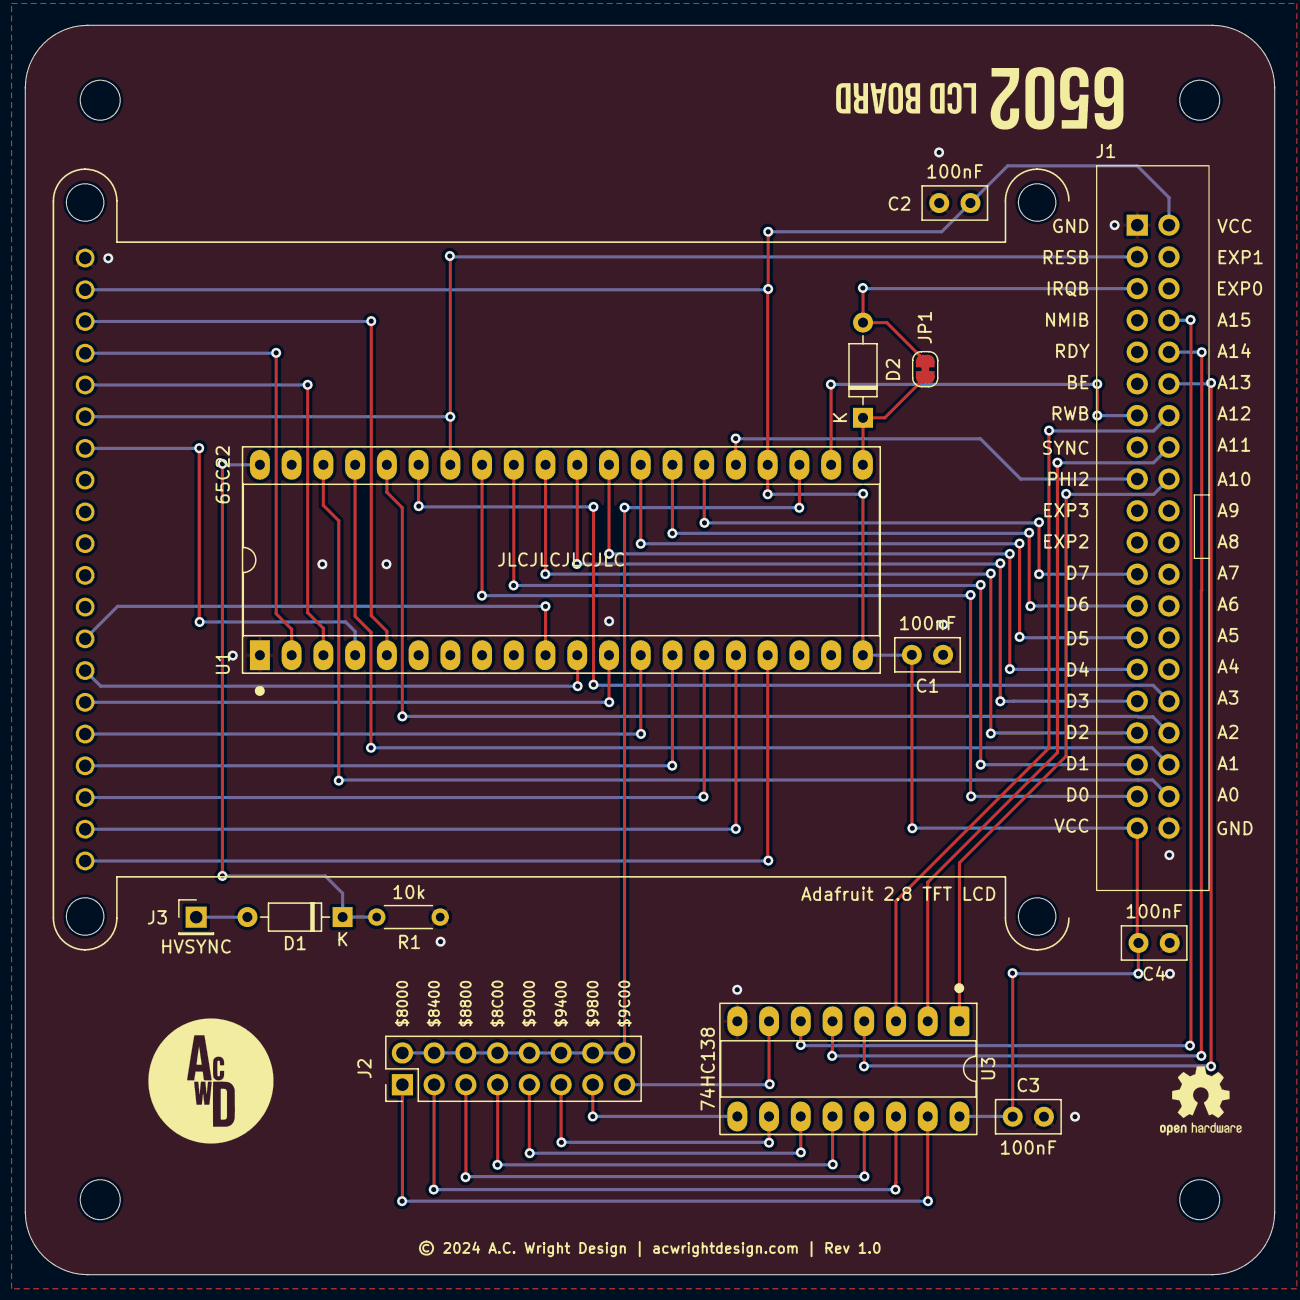
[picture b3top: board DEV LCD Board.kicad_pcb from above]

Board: 2 copper layers, 100.0 x 100.0 mm, 18 parts (0 on the bottom side), 48 nets.

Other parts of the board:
H1, H2, H3, H4: MountingHole; MountingHole_3.2mm_M3

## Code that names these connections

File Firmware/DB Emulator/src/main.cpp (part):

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  pinMode(D6, INPUT);
  pinMode(D7, INPUT);

  pinMode(RESB, INPUT);
  pinMode(SYNC, INPUT);
  pinMode(RWB, INPUT);
  pinMode(PHI2, OUTPUT);
  digitalWrite(PHI2, HIGH);  // Set high to turn on onboard LED
  pinMode(IRQB, INPUT);
  pinMode(NMIB, INPUT);
  pinMode(RDY, INPUT);
  pinMode(BE, INPUT);

  // Switch inputs
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
#ifdef DEVBOARD_1
  pinMode(RESET_SWB, INPUT_PULLUP);
  pinMode(MOSI1, INPUT);
  pinMode(MISO1, INPUT);
  pinMode(SCK1, INPUT);
  pinMode(CS, INPUT);
#endif
}
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
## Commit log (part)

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2026-05-03 Cleanup DEV project
2026-05-04 Finish DEV cleanup
2026-05-04 Uppercase DEV
2026-05-04 Fix case-sensitive file and folder names (Dev -> DEV)
2026-05-16 Add BOMs
2026-05-19 Finish BOM and add to README
2026-05-19 Restore exclude from BOM
2026-05-24 Update Dev Output Board silkscreen
2026-06-11 README fix
2026-06-15 Change pull up resistor values
2026-06-16 Remove BOM CSV's
2026-06-18 Revert pull-up resistor value change

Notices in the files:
Firmware/DB Emulator/src/main.cpp:
© 2024 A.C. Wright Design |");
Hardware/DEV Board/Rev 1.1/DEV Board.kicad_pcb:
© 2024 A.C. Wright Design | acwrightdesign.com | Rev 1.1
Hardware/DEV LCD Board/Rev 1.0/DEV LCD Board.kicad_pcb:
© 2024 A.C. Wright Design | acwrightdesign.com | Rev 1.0
